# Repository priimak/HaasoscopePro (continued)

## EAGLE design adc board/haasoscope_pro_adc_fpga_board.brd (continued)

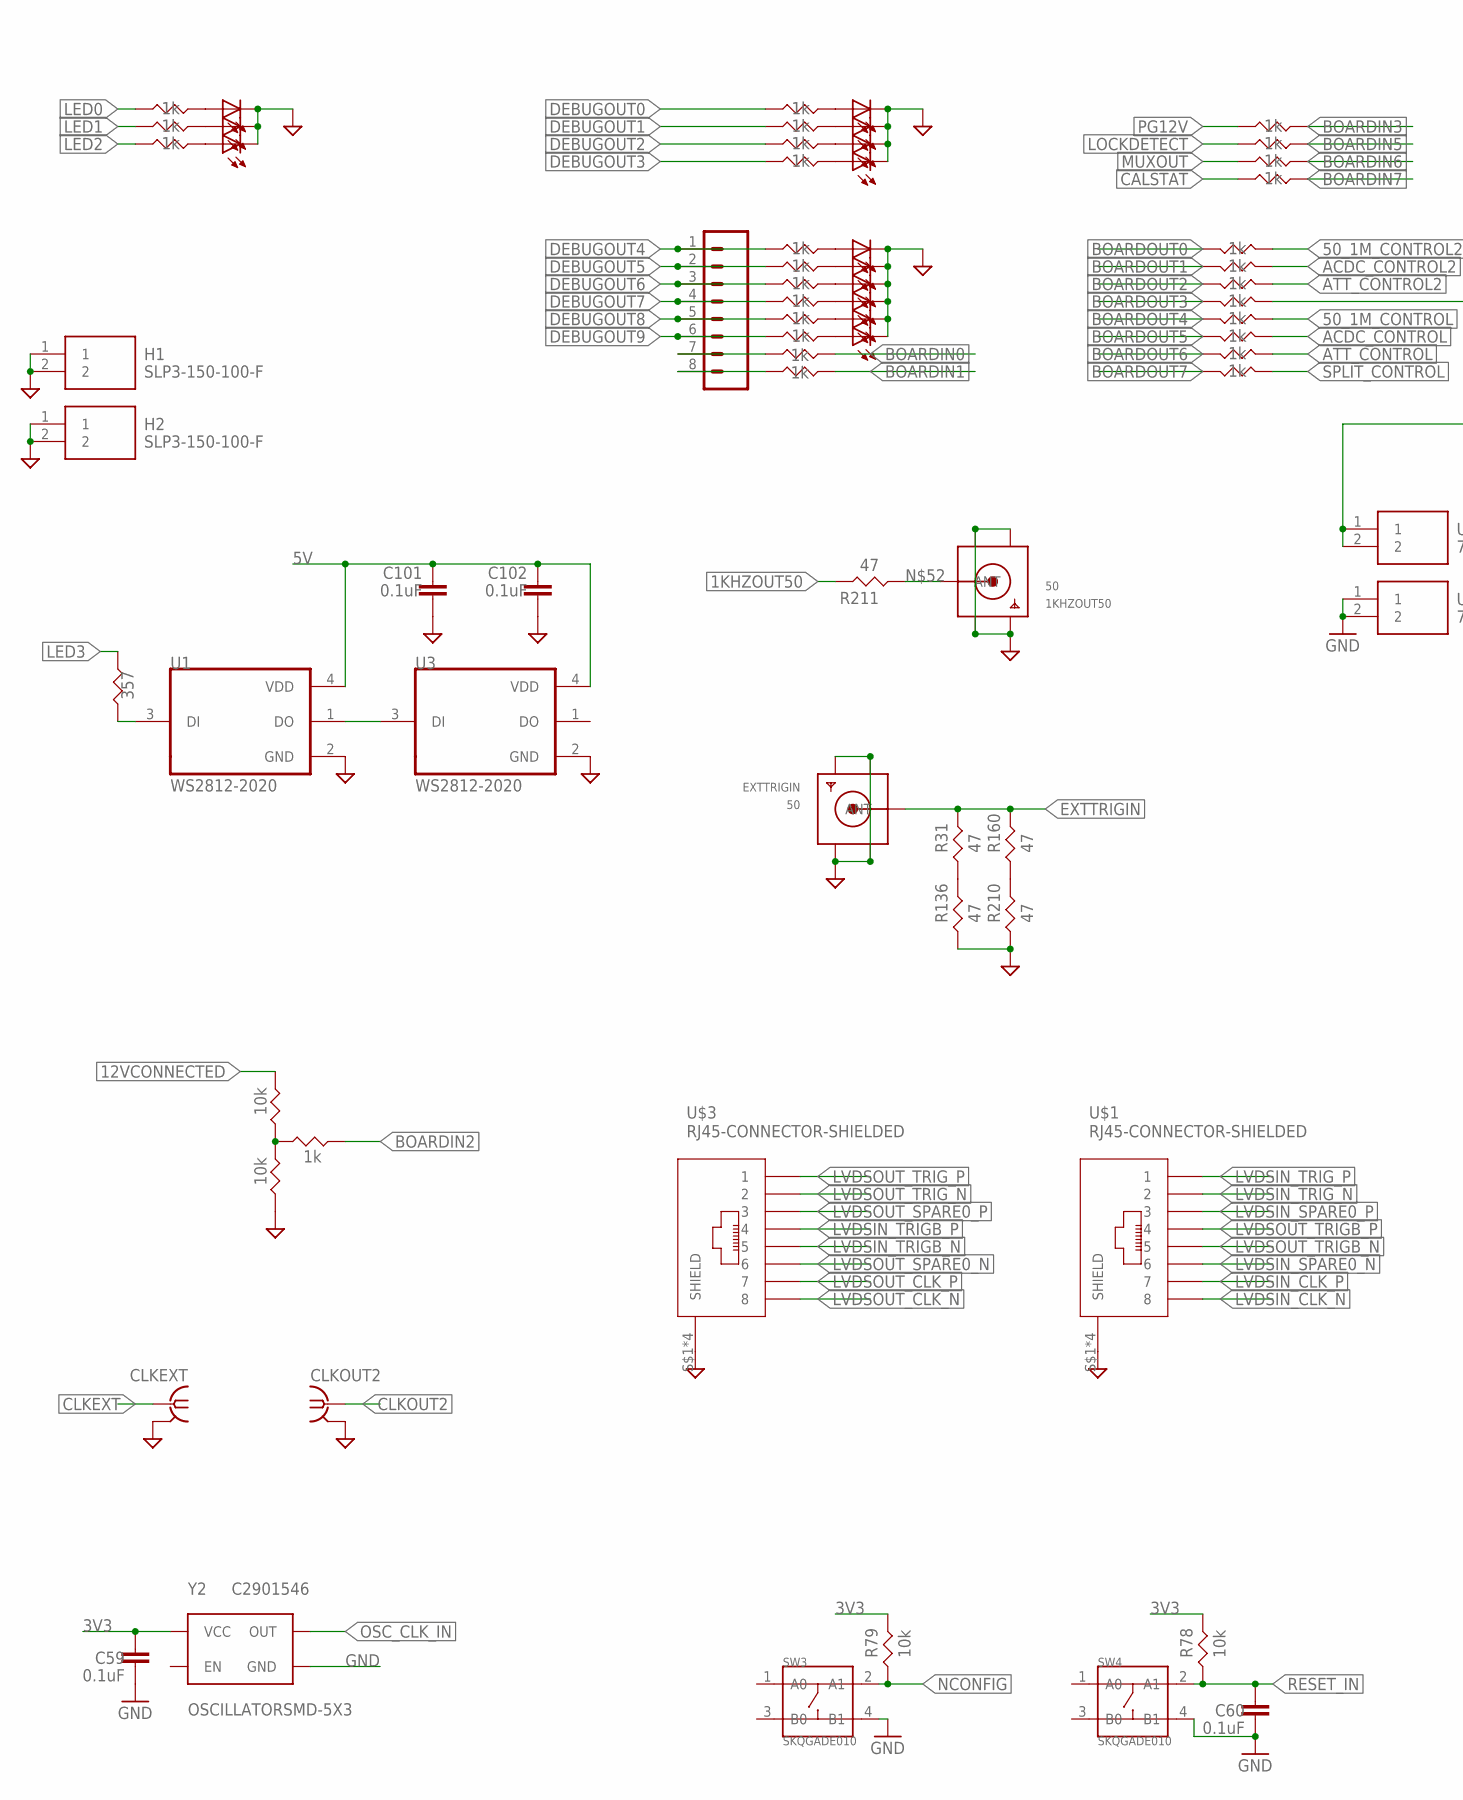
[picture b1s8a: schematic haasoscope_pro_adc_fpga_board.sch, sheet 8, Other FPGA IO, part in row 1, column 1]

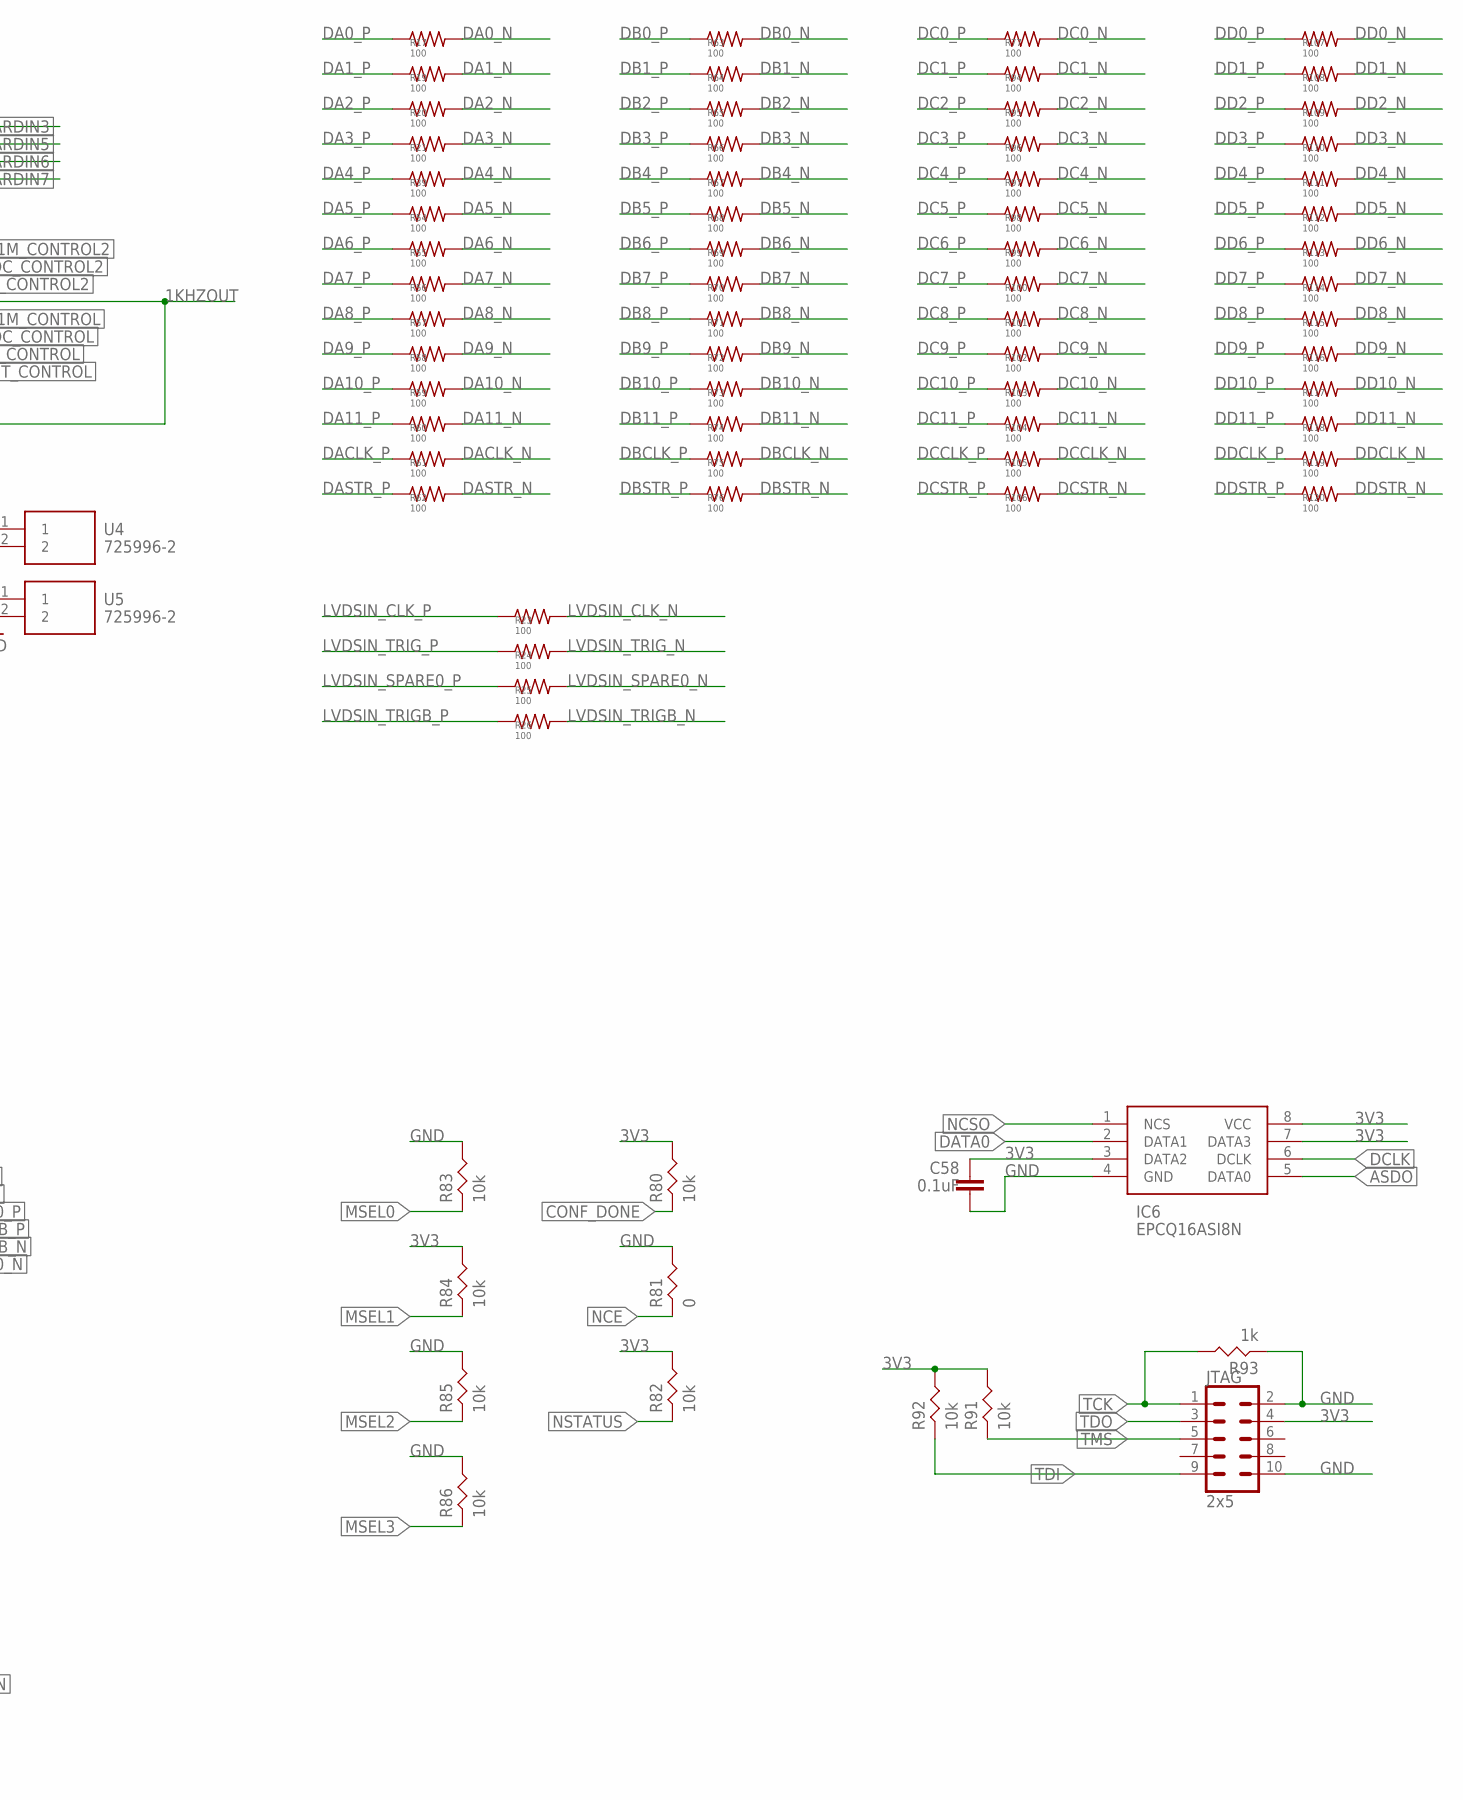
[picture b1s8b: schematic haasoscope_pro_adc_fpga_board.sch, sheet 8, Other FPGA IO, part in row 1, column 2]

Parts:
1KHZOUT50: 50; SMA_EDGELAUNCH
C58, C59, C60, C101, C102: 0.1uF; RESC0402_N
CLKEXT: BU-SMB-V
CLKOUT2: BU-SMB-V
EXTTRIGIN: 50; SMA_EDGELAUNCH
H1, H2: SLP3-150-100-F; SLP3150100F
IC6: EPCQ16ASI8N; SOIC127P600X175-8N
J11: 8pin; 1X08
JTAG: 2x5; 2X5-SHROUDED
LED25, LED26, LED27, LED28, LED29, LED30, LED41, LED42, LED43, LED45, LED46, LED47, LED48: red; CHIP-LED0603
R6, R7, R8, R9, R10, R11, R12, R13, R16, R22, R32, R33, R34, R35, R36, R37, R46, R47, R48, R49, R51, R52, R53, R93, R206, R236, R238, R243, R244: 1k; RES-0402
R17, R19, R20, R21, R23, R24, R25, R26, R39, R54, R55, R56, R57, R58, R59, R60, R61, R62, R63, R64, R65, R66, R67, R68, R69, R70, R71, R72, R73, R74, R75, R76, R77, R94, R95, R96, R97, R98, R99, R100, R101, R102, R103, R104, R105, R106, R107, R108, R109, R110, R111, R112, R113, R114, R115, R116, R117, R118, R119, R120: 100; R0201
R31, R136, R160, R210, R211: 47; RES-0402
R50: 357; RES-0402
R78, R79, R80, R82, R83, R84, R85, R86, R91, R92, R167, R246: 10k; RES-0402
R81: 0; RES-0402
SW3, SW4: SKQGADE010; SW4-SMD-5.2X5.2X1.5MM
U1, U3: WS2812-2020; LED_WS2812-2020
U4, U5: 725996-2; 7259962
U$1, U$3: RJ45-CONNECTOR-SHIELDED; RJ45_THT_RA_AMPH-FRJAE448
Y2: OSCILLATORSMD-5X3; OSCILLATOR-SMD-5X3.2; LCSC C2901546

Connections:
1KHZOUT: R206.P$1, U4.1, U4.2
1KHZOUT50: R211.P$2; also elsewhere on the board
3V3: C58.2, C59.2, IC6.3 (DATA2), IC6.7 (DATA3), IC6.8 (VCC), JTAG.4, R78.P$2, R79.P$2, R80.P$2, R82.P$2, R84.P$2, R91.P$2, R92.P$2, Y2.4 (VCC); also elsewhere on the board
5V: C101.2, C102.2, U1.4 (VDD), U3.4 (VDD); also elsewhere on the board
12VCONNECTED: R167.P$2; also elsewhere on the board
50_1M_CONTROL: R8.P$1; also elsewhere on the board
50_1M_CONTROL2: R12.P$1; also elsewhere on the board
ACDC_CONTROL: R9.P$1; also elsewhere on the board
ACDC_CONTROL2: R13.P$1; also elsewhere on the board
ASDO: IC6.5 (DATA0); also elsewhere on the board
ATT_CONTROL: R10.P$1; also elsewhere on the board
ATT_CONTROL2: R22.P$1; also elsewhere on the board
BOARDIN0: R243.P$1; also elsewhere on the board
BOARDIN1: R244.P$1; also elsewhere on the board
BOARDIN2: R238.P$2; also elsewhere on the board
BOARDIN3: R236.P$2; also elsewhere on the board
BOARDIN5: R7.P$2; also elsewhere on the board
BOARDIN6: R6.P$2; also elsewhere on the board
BOARDIN7: R16.P$2; also elsewhere on the board
BOARDOUT0: R12.P$2; also elsewhere on the board
BOARDOUT1: R13.P$2; also elsewhere on the board
BOARDOUT2: R22.P$2; also elsewhere on the board
BOARDOUT3: R206.P$2; also elsewhere on the board
BOARDOUT4: R8.P$2; also elsewhere on the board
BOARDOUT5: R9.P$2; also elsewhere on the board
BOARDOUT6: R10.P$2; also elsewhere on the board
BOARDOUT7: R11.P$2; also elsewhere on the board
CALSTAT: R16.P$1; also elsewhere on the board
CLKEXT: CLKEXT.1; also elsewhere on the board
CLKOUT2: CLKOUT2.1; also elsewhere on the board
CONF_DONE: R80.P$1; also elsewhere on the board
DA0_N: R17.2; also elsewhere on the board
DA0_P: R17.1; also elsewhere on the board
DA1_N: R19.2; also elsewhere on the board
DA1_P: R19.1; also elsewhere on the board
DA2_N: R20.2; also elsewhere on the board
DA2_P: R20.1; also elsewhere on the board
DA3_N: R21.2; also elsewhere on the board
DA3_P: R21.1; also elsewhere on the board
DA4_N: R39.2; also elsewhere on the board
DA4_P: R39.1; also elsewhere on the board
DA5_N: R54.2; also elsewhere on the board
DA5_P: R54.1; also elsewhere on the board
DA6_N: R55.2; also elsewhere on the board
DA6_P: R55.1; also elsewhere on the board
DA7_N: R56.2; also elsewhere on the board
DA7_P: R56.1; also elsewhere on the board
DA8_N: R57.2; also elsewhere on the board
DA8_P: R57.1; also elsewhere on the board
DA9_N: R58.2; also elsewhere on the board
DA9_P: R58.1; also elsewhere on the board
DA10_N: R59.2; also elsewhere on the board
DA10_P: R59.1; also elsewhere on the board
DA11_N: R60.2; also elsewhere on the board
DA11_P: R60.1; also elsewhere on the board
DACLK_N: R61.2; also elsewhere on the board
DACLK_P: R61.1; also elsewhere on the board
DASTR_N: R62.2; also elsewhere on the board
DASTR_P: R62.1; also elsewhere on the board
DATA0: IC6.2 (DATA1); also elsewhere on the board
DB0_N: R63.2; also elsewhere on the board
DB0_P: R63.1; also elsewhere on the board
DB1_N: R64.2; also elsewhere on the board
DB1_P: R64.1; also elsewhere on the board
DB2_N: R65.2; also elsewhere on the board
DB2_P: R65.1; also elsewhere on the board
DB3_N: R66.2; also elsewhere on the board
DB3_P: R66.1; also elsewhere on the board
DB4_N: R67.2; also elsewhere on the board
DB4_P: R67.1; also elsewhere on the board
DB5_N: R68.2; also elsewhere on the board
DB5_P: R68.1; also elsewhere on the board
DB6_N: R69.2; also elsewhere on the board
DB6_P: R69.1; also elsewhere on the board
DB7_N: R70.2; also elsewhere on the board
DB7_P: R70.1; also elsewhere on the board
DB8_N: R71.2; also elsewhere on the board
DB8_P: R71.1; also elsewhere on the board
DB9_N: R72.2; also elsewhere on the board
DB9_P: R72.1; also elsewhere on the board
DB10_N: R73.2; also elsewhere on the board
DB10_P: R73.1; also elsewhere on the board
DB11_N: R74.2; also elsewhere on the board
DB11_P: R74.1; also elsewhere on the board
DBCLK_N: R75.2; also elsewhere on the board
DBCLK_P: R75.1; also elsewhere on the board
DBSTR_N: R76.2; also elsewhere on the board
DBSTR_P: R76.1; also elsewhere on the board
DC0_N: R77.2; also elsewhere on the board
DC0_P: R77.1; also elsewhere on the board
DC1_N: R94.2; also elsewhere on the board
DC1_P: R94.1; also elsewhere on the board
DC2_N: R95.2; also elsewhere on the board
DC2_P: R95.1; also elsewhere on the board
DC3_N: R96.2; also elsewhere on the board
DC3_P: R96.1; also elsewhere on the board
DC4_N: R97.2; also elsewhere on the board
DC4_P: R97.1; also elsewhere on the board
DC5_N: R98.2; also elsewhere on the board
DC5_P: R98.1; also elsewhere on the board
DC6_N: R99.2; also elsewhere on the board
DC6_P: R99.1; also elsewhere on the board
DC7_N: R100.2; also elsewhere on the board
DC7_P: R100.1; also elsewhere on the board
DC8_N: R101.2; also elsewhere on the board
DC8_P: R101.1; also elsewhere on the board
DC9_N: R102.2; also elsewhere on the board
DC9_P: R102.1; also elsewhere on the board
DC10_N: R103.2; also elsewhere on the board
DC10_P: R103.1; also elsewhere on the board
DC11_N: R104.2; also elsewhere on the board
DC11_P: R104.1; also elsewhere on the board
DCCLK_N: R105.2; also elsewhere on the board
DCCLK_P: R105.1; also elsewhere on the board
DCLK: IC6.6 (DCLK); also elsewhere on the board
DCSTR_N: R106.2; also elsewhere on the board
DCSTR_P: R106.1; also elsewhere on the board
DD0_N: R107.2; also elsewhere on the board
DD0_P: R107.1; also elsewhere on the board
DD1_N: R108.2; also elsewhere on the board
DD1_P: R108.1; also elsewhere on the board
DD2_N: R109.2; also elsewhere on the board
DD2_P: R109.1; also elsewhere on the board
DD3_N: R110.2; also elsewhere on the board
DD3_P: R110.1; also elsewhere on the board
DD4_N: R111.2; also elsewhere on the board
DD4_P: R111.1; also elsewhere on the board
DD5_N: R112.2; also elsewhere on the board
DD5_P: R112.1; also elsewhere on the board
DD6_N: R113.2; also elsewhere on the board
DD6_P: R113.1; also elsewhere on the board
DD7_N: R114.2; also elsewhere on the board
DD7_P: R114.1; also elsewhere on the board
DD8_N: R115.2; also elsewhere on the board
DD8_P: R115.1; also elsewhere on the board
DD9_N: R116.2; also elsewhere on the board
DD9_P: R116.1; also elsewhere on the board
DD10_N: R117.2; also elsewhere on the board
DD10_P: R117.1; also elsewhere on the board
DD11_N: R118.2; also elsewhere on the board
DD11_P: R118.1; also elsewhere on the board
DDCLK_N: R119.2; also elsewhere on the board
DDCLK_P: R119.1; also elsewhere on the board
DDSTR_N: R120.2; also elsewhere on the board
DDSTR_P: R120.1; also elsewhere on the board
DEBUGOUT0: R49.P$1; also elsewhere on the board
DEBUGOUT1: R48.P$1; also elsewhere on the board
DEBUGOUT2: R47.P$1; also elsewhere on the board
DEBUGOUT3: R46.P$1; also elsewhere on the board
DEBUGOUT4: J11.1, R37.P$1; also elsewhere on the board
DEBUGOUT5: J11.2, R36.P$1; also elsewhere on the board
DEBUGOUT6: J11.3, R35.P$1; also elsewhere on the board
DEBUGOUT7: J11.4, R34.P$1; also elsewhere on the board
DEBUGOUT8: J11.5, R33.P$1; also elsewhere on the board
DEBUGOUT9: J11.6, R32.P$1; also elsewhere on the board
EXTTRIGIN: EXTTRIGIN.P (ANT), R31.P$2, R160.P$2; also elsewhere on the board
GND: 1KHZOUT50.GND@1 (GND4), 1KHZOUT50.GND@2 (GND3), 1KHZOUT50.GND@3 (GND2), 1KHZOUT50.GND@4 (GND1), C58.1, C59.1, C60.1, C101.1, C102.1, CLKEXT.2, CLKEXT.3 (2), CLKEXT.4 (2), CLKEXT.5 (2), CLKOUT2.2, CLKOUT2.3 (2), CLKOUT2.4 (2), CLKOUT2.5 (2), EXTTRIGIN.GND@1 (GND4), EXTTRIGIN.GND@2 (GND3), EXTTRIGIN.GND@3 (GND2), EXTTRIGIN.GND@4 (GND1), H1.1, H1.2, H2.1, H2.2, IC6.4 (GND), JTAG.2, JTAG.10, LED25.C, LED26.C, LED27.C, LED28.C, LED29.C, LED30.C, LED41.C, LED42.C, LED43.C, LED45.C, LED46.C, LED47.C, LED48.C, R81.P$2, R83.P$2, R85.P$2, R86.P$2, R93.P$1, R136.P$1, R210.P$1, R246.P$1, SW3.4 (B1), SW4.4 (B1), U1.2 (GND), U3.2 (GND), U5.1, U5.2, U$1.S$1 (SHIELD), U$1.S$2 (SHIELD), U$1.S$3 (SHIELD), U$1.S$4 (SHIELD), U$3.S$1 (SHIELD), U$3.S$2 (SHIELD), U$3.S$3 (SHIELD), U$3.S$4 (SHIELD), Y2.2 (GND); also elsewhere on the board
LED0: R53.P$1; also elsewhere on the board
LED1: R52.P$1; also elsewhere on the board
LED2: R51.P$1; also elsewhere on the board
LED3: R50.P$1; also elsewhere on the board
LOCKDETECT: R7.P$1; also elsewhere on the board
LVDSIN_CLK_N: R23.2, U$1.P$8 (8); also elsewhere on the board
LVDSIN_CLK_P: R23.1, U$1.P$7 (7); also elsewhere on the board
LVDSIN_SPARE0_N: R25.2, U$1.P$6 (6); also elsewhere on the board
LVDSIN_SPARE0_P: R25.1, U$1.P$3 (3); also elsewhere on the board
LVDSIN_TRIGB_N: R26.2, U$3.P$5 (5); also elsewhere on the board
LVDSIN_TRIGB_P: R26.1, U$3.P$4 (4); also elsewhere on the board
LVDSIN_TRIG_N: R24.2, U$1.P$2 (2); also elsewhere on the board
LVDSIN_TRIG_P: R24.1, U$1.P$1 (1); also elsewhere on the board
LVDSOUT_CLK_N: U$3.P$8 (8); also elsewhere on the board
LVDSOUT_CLK_P: U$3.P$7 (7); also elsewhere on the board
LVDSOUT_SPARE0_N: U$3.P$6 (6); also elsewhere on the board
LVDSOUT_SPARE0_P: U$3.P$3 (3); also elsewhere on the board
LVDSOUT_TRIGB_N: U$1.P$5 (5); also elsewhere on the board
LVDSOUT_TRIGB_P: U$1.P$4 (4); also elsewhere on the board
LVDSOUT_TRIG_N: U$3.P$2 (2); also elsewhere on the board
LVDSOUT_TRIG_P: U$3.P$1 (1); also elsewhere on the board
MSEL0: R83.P$1; also elsewhere on the board
MSEL1: R84.P$1; also elsewhere on the board
MSEL2: R85.P$1; also elsewhere on the board
MSEL3: R86.P$1; also elsewhere on the board
MUXOUT: R6.P$1; also elsewhere on the board
unnamed: R31.P$1, R136.P$2
unnamed: LED25.A, R37.P$2
unnamed: LED26.A, R36.P$2
unnamed: LED27.A, R35.P$2
unnamed: LED28.A, R34.P$2
unnamed: LED29.A, R33.P$2
unnamed: LED30.A, R32.P$2
unnamed: R160.P$1, R210.P$2
unnamed: LED41.A, R53.P$2
unnamed: LED42.A, R52.P$2
unnamed: LED43.A, R51.P$2
unnamed: R50.P$2, U1.3 (DI)
unnamed: LED45.A, R49.P$2
unnamed: LED46.A, R48.P$2
unnamed: LED47.A, R47.P$2
unnamed: LED48.A, R46.P$2
unnamed: 1KHZOUT50.P (ANT), R211.P$1
unnamed: J11.7, R243.P$2
unnamed: J11.8, R244.P$2
unnamed: R167.P$1, R238.P$1, R246.P$2
unnamed: U1.1 (DO), U3.3 (DI)
NCE: R81.P$1; also elsewhere on the board
NCONFIG: R79.P$1, SW3.2 (A1); also elsewhere on the board
NCSO: IC6.1 (NCS); also elsewhere on the board
NSTATUS: R82.P$1; also elsewhere on the board
OSC_CLK_IN: Y2.3 (OUT); also elsewhere on the board
PG12V: R236.P$1; also elsewhere on the board
RESET_IN: C60.2, R78.P$1, SW4.2 (A1); also elsewhere on the board
SPLIT_CONTROL: R11.P$1; also elsewhere on the board
TCK: JTAG.1, R93.P$2; also elsewhere on the board
TDI: JTAG.9, R92.P$1; also elsewhere on the board
TDO: JTAG.3; also elsewhere on the board
TMS: JTAG.5, R91.P$1; also elsewhere on the board

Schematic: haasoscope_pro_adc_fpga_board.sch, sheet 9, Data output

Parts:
C114, C115, C116, C117, C119, C121, C122, C123, C124, C125: 0.1uF; RESC0402_N
C118, C120, C126: 10uF; RESC0805_N
C127, C128: 16pF; RESC0402_N
FB2: 50mΩ 220Ω@100MHz 0603; 0603
IC8: FT232HQ; QFN48_8MM; JLC_ROTATION 270
IC9: 93LC56B; SOT23-6; LCSC C190271
R27, R38, R121, R123: 10k; RES-0402
R28, R29, R40, R41, R157, R179: 1k; RES-0402
R182, R183: 5.1k; RES-0402
R184: 39; RES-0402
X1: USBC; USB_C_CUSB31-CFM2AX-01-X
Y3: 12MHz; CRYSTAL-SMD-5X3; LCSC C2901628

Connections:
3V3: IC8.32 (ACBUS8), R121.P$2, R123.P$2; also elsewhere on the board
5V: C117.2, IC8.40 (VREGIN); also elsewhere on the board
CC1: R183.P$2, X1.A5 (CC1)
CC2: R182.P$2, X1.B5 (CC2)
FTDI_AC0_RXF: IC8.21 (ACBUS0/TXDEN); also elsewhere on the board
FTDI_AC1_TXE: IC8.25 (ACBUS1); also elsewhere on the board
FTDI_AC2_RD: IC8.26 (ACBUS2); also elsewhere on the board
FTDI_AC3_WR: IC8.27 (ACBUS3/RXLED#); also elsewhere on the board
FTDI_AC4_SIWU: IC8.28 (ACBUS4/TXLED#), R121.P$1
FTDI_AC5_CLK: R184.P$2; also elsewhere on the board
FTDI_AC6_OE: IC8.30 (ACBUS6); also elsewhere on the board
FTDI_AC7_PWRSAV: IC8.31 (ACBUS7), R123.P$1
FTDI_DATA0: IC8.13 (ADBUS0/TXD); also elsewhere on the board
FTDI_DATA1: IC8.14 (ADBUS1/RXD); also elsewhere on the board
FTDI_DATA2: IC8.15 (ADBUS2/RTS#); also elsewhere on the board
FTDI_DATA3: IC8.16 (ADBUS3/CTS#); also elsewhere on the board
FTDI_DATA4: IC8.17 (ADBUS4/DTR#); also elsewhere on the board
FTDI_DATA5: IC8.18 (ADBUS5/DSR#); also elsewhere on the board
FTDI_DATA6: IC8.19 (ADBUS6/DCD#); also elsewhere on the board
FTDI_DATA7: IC8.20 (ADBUS7/RI#); also elsewhere on the board
GND: C114.1, C115.1, C116.1, C117.1, C118.1, C119.1, C120.1, C121.1, C122.1, C123.1, C124.1, C125.1, C126.1, C127.2, C128.2, IC8.4 (AGND), IC8.9 (AGND), IC8.10 (GND), IC8.11 (GND), IC8.22 (GND), IC8.23 (GND), IC8.33 (ACBUS9), IC8.35 (GND), IC8.36 (GND), IC8.41 (AGND), IC8.42 (TEST), IC8.47 (GND), IC8.48 (GND), IC8.THERMAL (PAD), IC9.2 (GND), R41.P$1, R182.P$1, R183.P$1, X1.A1B12 (GND), X1.B1A12 (GND); also elsewhere on the board
unnamed: R27.P$1, R28.P$2
unnamed: R28.P$1, R29.P$2
unnamed: R38.P$1, R40.P$2
unnamed: R40.P$1, R41.P$2
unnamed: R157.P$1, R179.P$2
unnamed: C127.1, IC8.1 (OSCIN), Y3.3 (2)
unnamed: C128.1, IC8.2 (OSCOUT), Y3.1
unnamed: IC8.34 (!RESET), R27.P$2
unnamed: IC8.43 (EEDATA), IC9.3 (DI), R157.P$2
unnamed: IC8.45 (EECS), IC9.5 (CS)
unnamed: IC8.44 (EECLK), IC9.4 (CLK)
unnamed: IC9.1 (DO), R179.P$1
unnamed: IC8.29 (ACBUS5), R184.P$1
REF: IC8.5 (REF), R38.P$2
USB_D_N: IC8.7 (USBD+), X1.A6 (D+), X1.B6 (D+)
USB_D_P: IC8.6 (USBD-), X1.A7 (D-), X1.B7 (D-)
VBUS: C118.2, FB2.1, X1.A4B9 (VBUS), X1.B4A9 (VBUS)
VBUSOUT: C126.2, FB2.2; also elsewhere on the board
VCC1V8: C114.2, IC8.38 (VCCCORE)
VCC3V3: C116.2, C119.2, C120.2, C121.2, C122.2, C123.2, C124.2, C125.2, IC8.3 (VPHY), IC8.8 (VPLL), IC8.12 (VCCIO), IC8.24 (VCCIO), IC8.39 (VCCD), IC8.46 (VCCIO), IC9.6 (VCC), R29.P$1
VCCA_FTDI: C115.2, IC8.37 (VCCA)

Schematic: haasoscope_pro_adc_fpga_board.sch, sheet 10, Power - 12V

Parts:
C81, C166, C290, C291, C292, C293: 22uF; RESC0805_N
C171, C172: 1000uF; EEE0JA152UAP; LCSC C401766
C242, C243, C287, C289, C319, C320, C321, C322: 10uF; RESC0805_N
C283, C318: 0.1uF; RESC0402_N; LCSC C307331
C284, C286: 0.1uF; RESC0402_N
C285: 1uF; RESC0402_N
CN2: 12Vin; DCJACK_2MM_PTH
J30, J45, J46: 2p-2.54; H2-2.54
L2, L14: 10uH; CDRH125; LCSC C339970
LED2, LED3, LED4: red; CHIP-LED0603
PS14: LMR33630ADDA; SOIC127P600X170-9N; LCSC C841384
Q2: FDN340P; SOT-23; MPN P-MOS AO3401A
R148, R151, R212, R234, R239: 10k; RES-0402
R152, R165, R217, R235: 5.1k; RES-0402
R233: 100k; RES-0402
R237: 1k; RES-0402

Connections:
5V: C166.1, C172.1 (+), J45.1, L2.2, R148.P$2; also elsewhere on the board
5VDIRTY: C81.1, C171.1 (+), C286.1, C287.1, C289.1, C290.1, C291.1, C292.1, C293.1, J46.2, L2.1, L14.2, LED3.A, Q2.2 (S), R233.P$2, R237.P$2
12V: C242.1, C283.1, C319.1, C320.1, CN2.PWR, J30.2, LED2.A, PS14.2 (VIN), PS14.3 (EN)
12VCONNECTED: CN2.GNDBREAK, R237.P$1, R239.P$1; also elsewhere on the board
GND: C81.2, C166.2, C171.2 (-), C172.2 (-), C243.2, C285.2, C286.2, C287.2, C289.2, C290.2, C291.2, C292.2, C293.2, C318.2, C321.2, C322.2, CN2.GND, J30.1, J45.2, J46.1, PS14.1 (PGND), PS14.9 (EP), R148.P$1, R152.P$1, R165.P$1, R217.P$1, R235.P$1; also elsewhere on the board
unnamed: R151.P$2, R234.P$1
unnamed: R151.P$1, R152.P$2
unnamed: LED2.C, R217.P$2
unnamed: LED3.C, R235.P$2
unnamed: Q2.1 (G), R239.P$2
unnamed: LED4.C, R165.P$2
unnamed: C242.2, C243.1
unnamed: C284.1, L14.1, PS14.8 (SW)
unnamed: C284.2, PS14.7 (BOOT)
unnamed: PS14.5 (FB), R233.P$1, R234.P$2
unnamed: C285.1, PS14.6 (VCC)
unnamed: C283.2, C318.1
unnamed: C319.2, C321.1
unnamed: C320.2, C322.1
PG12V: PS14.4 (PG), R212.P$2; also elsewhere on the board
VBUSOUT: LED4.A, Q2.3 (D); also elsewhere on the board
VCCIO2V5: R212.P$1; also elsewhere on the board

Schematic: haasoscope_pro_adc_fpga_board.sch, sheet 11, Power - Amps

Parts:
C73, C74, C77, C250, C252, C254, C279, C280, C282: 0.1uF; RESC0402_N
C76, C251, C253, C288: 10uF; RESC0805_N
C83: 1000uF; EEE0JA152UAP; LCSC C401766
C281: 1uF; RESC0402_N
C294, C295, C296, C297: 22uF; RESC0805_N
D10: B340A; SMA-DIODE; LCSC C64982
IC10, IC25: TPS72325DBVR; SOT95P280X145-5N
IC26: TPS7A7200RGTR; QFN50P300X300X100-17N
J4, J34, J35, J44: 2p-2.54; H2-2.54
L13: 10uH; CDRH125; LCSC C339970
PS13: LMR33630ADDA; SOIC127P600X170-9N; LCSC C841384
R209, R231, R232: 100k; RES-0402
R216: 10k; RES-0402

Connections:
2V5+: C253.1, C254.1, IC26.1 (SNS), IC26.15 (OUT_1), IC26.16 (OUT_2), J35.2, R216.P$1; also elsewhere on the board
2V5-1: C251.1, IC25.5 (OUT), J34.1; also elsewhere on the board
2V5-2: C76.1, IC10.5 (OUT), J4.1; also elsewhere on the board
3V0-: C77.1, C83.2 (-), C252.1, C279.2, C281.2, C282.2, C288.2, C294.2, C295.2, C296.2, C297.2, D10.A, IC10.2 (IN), IC25.2 (IN), J44.2, PS13.1 (PGND), PS13.9 (EP), R209.P$1, R232.P$1
3V3: C73.1, IC26.12 (EN), IC26.13 (IN_1), IC26.14 (IN_2); also elsewhere on the board
5V: C279.1, C288.1, PS13.2 (VIN), PS13.3 (EN); also elsewhere on the board
GND: C73.2, C74.2, C76.2, C77.2, C83.1 (+), C250.2, C251.2, C252.2, C253.2, C254.2, C282.1, C294.1, C295.1, C296.1, C297.1, D10.C, IC10.1 (GND), IC25.1 (GND), IC26.7 (GND), IC26.8 (400MV), IC26.10 (1.6V), IC26.17 (EP), J4.2, J34.2, J35.1, J44.1, L13.2, R231.P$2; also elsewhere on the board
unnamed: C74.1, IC10.4 (NR/FB)
unnamed: C250.1, IC25.4 (NR/FB)
unnamed: C280.1, L13.1, PS13.8 (SW)
unnamed: C280.2, PS13.7 (BOOT)
unnamed: PS13.5 (FB), R209.P$2, R231.P$1, R232.P$2
unnamed: C281.1, PS13.6 (VCC)
PG25: IC26.3 (PG), R216.P$2

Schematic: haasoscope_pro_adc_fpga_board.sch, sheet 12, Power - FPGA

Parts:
C52, C170, C173, C257: 10uF; RESC0805_N
C53, C54, C258, C271, C272, C274, C275, C276, C278: 0.1uF; RESC0402_N
C99, C168: 1000uF; EEE0JA152UAP; LCSC C401766
C273, C277: 1uF; RESC0402_N
C298, C299, C300, C301, C302, C303, C304, C305: 22uF; RESC0805_N
IC7, IC28: TPS7A7200RGTR; QFN50P300X300X100-17N
J3, J37, J42, J43: 2p-2.54; H2-2.54
L11, L12: 10uH; CDRH125; LCSC C339970
PS11, PS12: LMR33630ADDA; SOIC127P600X170-9N; LCSC C841384
R137, R227, R229, R230: 100k; RES-0402
R161, R220: 10k; RES-0402
R228: 56k; RES-0402

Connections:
1V2: C52.1, C53.1, IC7.1 (SNS), IC7.15 (OUT_1), IC7.16 (OUT_2), J3.2, R161.P$1; also elsewhere on the board
1V5D: C54.1, C99.1 (+), C278.1, C298.1, C299.1, C300.1, C301.1, IC7.12 (EN), IC7.13 (IN_1), IC7.14 (IN_2), J43.1, L12.2, R229.P$2
2V5D: C257.1, C258.1, IC28.1 (SNS), IC28.15 (OUT_1), IC28.16 (OUT_2), J37.2, R220.P$1; also elsewhere on the board
2V8D: C168.1 (+), C274.1, C302.1, C303.1, C304.1, C305.1, IC28.12 (EN), IC28.13 (IN_1), IC28.14 (IN_2), J42.1, L11.2, R227.P$2
5V: C170.1, C173.1, C271.1, C275.1, PS11.2 (VIN), PS11.3 (EN), PS12.2 (VIN), PS12.3 (EN); also elsewhere on the board
GND: C52.2, C53.2, C54.2, C99.2 (-), C168.2 (-), C170.2, C173.2, C257.2, C258.2, C271.2, C273.2, C274.2, C275.2, C277.2, C278.2, C298.2, C299.2, C300.2, C301.2, C302.2, C303.2, C304.2, C305.2, IC7.5 (100MV), IC7.6 (200MV), IC7.7 (GND), IC7.8 (400MV), IC7.17 (EP), IC28.7 (GND), IC28.8 (400MV), IC28.10 (1.6V), IC28.17 (EP), J3.1, J37.1, J42.2, J43.2, PS11.1 (PGND), PS11.9 (EP), PS12.1 (PGND), PS12.9 (EP), R137.P$1, R228.P$1; also elsewhere on the board
unnamed: R137.P$2, R230.P$1
unnamed: C272.1, L11.1, PS11.8 (SW)
unnamed: C272.2, PS11.7 (BOOT)
unnamed: PS11.5 (FB), R227.P$1, R228.P$2
unnamed: C273.1, PS11.6 (VCC)
unnamed: C276.1, L12.1, PS12.8 (SW)
unnamed: C276.2, PS12.7 (BOOT)
unnamed: PS12.5 (FB), R229.P$1, R230.P$2
unnamed: C277.1, PS12.6 (VCC)
PG1V2: IC7.3 (PG), R161.P$2
PG2V5D: IC28.3 (PG), R220.P$2

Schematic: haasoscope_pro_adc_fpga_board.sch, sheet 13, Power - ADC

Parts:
C100, C165, C167: 1000uF; EEE0JA152UAP; LCSC C401766
C174, C175, C176, C244, C246, C248, C255: 10uF; RESC0805_N
C245, C247, C249, C256, C259, C260, C262, C263, C264, C266, C267, C268, C270: 0.1uF; RESC0402_N
C261, C265, C269: 1uF; RESC0402_N
C306, C307, C308, C309, C310, C311, C312, C313, C314, C315, C316, C317: 22uF; RESC0805_N
IC22, IC23, IC24, IC27: TPS7A7200RGTR; QFN50P300X300X100-17N
J31, J32, J33, J36, J39, J40, J41: 2p-2.54; H2-2.54
L1, L9, L10: 10uH; CDRH125; LCSC C339970
LED1: red; CHIP-LED0603
PS2, PS9, PS10: LMR33630ADDA; SOIC127P600X170-9N; LCSC C841384
R163, R221, R223, R224, R225, R226: 100k; RES-0402
R204, R205: 1M; RES-0402
R213, R214, R215, R219: 10k; RES-0402
R218: 5.1k; RES-0402
R222: 39k; RES-0402

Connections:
1V5: C165.1 (+), C266.1, C310.1, C311.1, C312.1, C313.1, IC24.13 (IN_1), IC24.14 (IN_2), J40.1, L9.2, R223.P$2
2V2: C167.1 (+), C270.1, C306.1, C307.1, C308.1, C309.1, IC23.12 (EN), IC23.13 (IN_1), IC23.14 (IN_2), IC27.12 (EN), IC27.13 (IN_1), IC27.14 (IN_2), J41.1, L10.2, R225.P$2
3V3: C244.1, C245.1, IC22.1 (SNS), IC22.15 (OUT_1), IC22.16 (OUT_2), J31.2, LED1.A, R213.P$1; also elsewhere on the board
3V7: C100.1 (+), C262.1, C314.1, C315.1, C316.1, C317.1, IC22.12 (EN), IC22.13 (IN_1), IC22.14 (IN_2), J39.1, L1.2, R221.P$2
5V: C174.1, C175.1, C176.1, C259.1, C263.1, C267.1, PS2.2 (VIN), PS2.3 (EN), PS9.2 (VIN), PS9.3 (EN), PS10.2 (VIN), PS10.3 (EN); also elsewhere on the board
GND: C100.2 (-), C165.2 (-), C167.2 (-), C174.2, C175.2, C176.2, C244.2, C245.2, C246.2, C247.2, C248.2, C249.2, C255.2, C256.2, C259.2, C261.2, C262.2, C263.2, C265.2, C266.2, C267.2, C269.2, C270.2, C306.2, C307.2, C308.2, C309.2, C310.2, C311.2, C312.2, C313.2, C314.2, C315.2, C316.2, C317.2, IC22.7 (GND), IC22.8 (400MV), IC22.9 (800MV), IC22.10 (1.6V), IC22.17 (EP), IC23.6 (200MV), IC23.7 (GND), IC23.8 (400MV), IC23.9 (800MV), IC23.17 (EP), IC24.6 (200MV), IC24.7 (GND), IC24.8 (400MV), IC24.17 (EP), IC27.6 (200MV), IC27.7 (GND), IC27.8 (400MV), IC27.9 (800MV), IC27.17 (EP), J31.1, J32.1, J33.1, J36.1, J39.2, J40.2, J41.2, PS2.1 (PGND), PS2.9 (EP), PS9.1 (PGND), PS9.9 (EP), PS10.1 (PGND), PS10.9 (EP), R163.P$1, R204.P$1, R205.P$1, R218.P$1, R222.P$1, R226.P$1; also elsewhere on the board
unnamed: R163.P$2, R224.P$1
unnamed: C260.1, L1.1, PS2.8 (SW)
unnamed: C260.2, PS2.7 (BOOT)
unnamed: PS2.5 (FB), R221.P$1, R222.P$2
unnamed: C261.1, PS2.6 (VCC)
unnamed: C264.1, L9.1, PS9.8 (SW)
unnamed: C264.2, PS9.7 (BOOT)
unnamed: PS9.5 (FB), R223.P$1, R224.P$2
unnamed: C265.1, PS9.6 (VCC)
unnamed: C268.1, L10.1, PS10.8 (SW)
unnamed: C268.2, PS10.7 (BOOT)
unnamed: PS10.5 (FB), R204.P$2, R205.P$2, R225.P$1, R226.P$2
unnamed: C269.1, PS10.6 (VCC)
unnamed: LED1.C, R218.P$2
PG1V1: IC24.3 (PG), R215.P$2
PG1V9: IC23.3 (PG), IC24.12 (EN), R214.P$2
PG1V9D: IC27.3 (PG), R219.P$2
PG3V3: IC22.3 (PG), R213.P$2
V11_IN: C248.1, C249.1, IC24.1 (SNS), IC24.15 (OUT_1), IC24.16 (OUT_2), J33.2, R215.P$1; also elsewhere on the board
V19_IN: C246.1, C247.1, IC23.1 (SNS), IC23.15 (OUT_1), IC23.16 (OUT_2), J32.2, R214.P$1; also elsewhere on the board
VLVDS_IN: C255.1, C256.1, IC27.1 (SNS), IC27.15 (OUT_1), IC27.16 (OUT_2), J36.2, R219.P$1; also elsewhere on the board

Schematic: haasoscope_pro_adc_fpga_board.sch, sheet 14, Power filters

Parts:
C5, C15, C25, C35, C45: NFM31PC276B0J3L; NFM31HK103R1H3L
C6, C8, C10, C13, C16, C18, C21, C24, C26, C28, C34, C36, C38, C40, C41, C42, C43, C46, C48: 10uF; RESC0805_N
C7, C9, C12, C17, C19, C20, C23, C27, C29, C31, C33, C37, C39, C47, C49, C61, C62, C63, C64, C65, C66, C67, C68, C69, C70, C71: 0.1uF; RESC0402_N
C11, C14, C22, C30, C32: 1uF; RESC0402_N
R15, R18, R87, R88, R89, R90: 0; RES-0402

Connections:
1V2: R88.P$1, R89.P$1; also elsewhere on the board
2V5D: R87.P$1, R90.P$1; also elsewhere on the board
3V3: R15.P$1, R18.P$1; also elsewhere on the board
GND: C5.2 (GND_1), C5.4 (GND_2), C6.1, C7.1, C8.1, C9.1, C10.1, C11.1, C12.1, C13.1, C14.1, C15.2 (GND_1), C15.4 (GND_2), C16.1, C17.1, C18.1, C19.1, C20.1, C21.1, C22.1, C23.1, C24.1, C25.2 (GND_1), C25.4 (GND_2), C26.1, C27.1, C28.1, C29.1, C30.1, C31.1, C32.1, C33.1, C34.1, C35.2 (GND_1), C35.4 (GND_2), C36.1, C37.1, C38.1, C39.1, C40.1, C41.1, C42.1, C43.1, C45.2 (GND_1), C45.4 (GND_2), C46.1, C47.1, C48.1, C49.1, C61.1, C62.1, C63.1, C64.1, C65.1, C66.1, C67.1, C68.1, C69.1, C70.1, C71.1; also elsewhere on the board
V11_IN: C35.1 (IN), C36.2, C37.2, C45.1 (IN), C46.2, C47.2; also elsewhere on the board
V19_IN: C15.1 (IN), C16.2, C17.2, C25.1 (IN), C26.2, C27.2; also elsewhere on the board
VA11: C21.2, C22.2, C23.2, C32.2, C33.2, C35.3 (OUT), C38.2, C39.2; also elsewhere on the board
VA19: C13.2, C14.2, C20.2, C25.3 (OUT), C28.2, C29.2; also elsewhere on the board
VCCA: C41.2, C71.2, R90.P$2; also elsewhere on the board
VCCINT: C43.2, C69.2, R88.P$2; also elsewhere on the board
VCCIO2V5: C40.2, C61.2, C62.2, C65.2, C66.2, C67.2, C68.2, R87.P$2; also elsewhere on the board
VCCIO3V3: C34.2, C63.2, C64.2, R18.P$2; also elsewhere on the board
VCCPLL: C42.2, C70.2, R89.P$2; also elsewhere on the board
VD11: C24.2, C30.2, C31.2, C45.3 (OUT), C48.2, C49.2; also elsewhere on the board
VDDD33: R15.P$2; also elsewhere on the board
VDDL19: C15.3 (OUT), C18.2, C19.2; also elsewhere on the board
VLVDS: C5.3 (OUT), C8.2, C9.2, C10.2, C11.2, C12.2; also elsewhere on the board
VLVDS_IN: C5.1 (IN), C6.2, C7.2; also elsewhere on the board

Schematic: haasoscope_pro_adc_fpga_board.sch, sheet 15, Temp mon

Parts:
C44, C50: 0.1uF; 0402_CAP
IC3: ADC122S021CIMM_NOPB; SOP65P490X110-8N
IC4: TLV9102IPWR; SOP65P640X120-8N
JST_FAN: Fan; 1X02
LED32: red; CHIP-LED0603
Q1: S8050; SOT-23; LCSC C7420370
R30: 1k; RES-0402
R122, R124, R126, R202, R203: 1k; 0402_RES
R125, R127, R130, R186, R198: 10k; 0402_RES
R128, R129: 0; 0402_RES
R207: NCP18WF104F03RC; R0603; MPN NCP18XH103F03RB; LCSC C13564
R208: 1k; R0402

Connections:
3V3: C44.1, C50.1, IC3.2 (VA), IC4.8 (V+), R127.1, R130.1; also elsewhere on the board
5V: JST_FAN.1; also elsewhere on the board
FAN-: JST_FAN.2, Q1.3 (C)
FAN_CONTROL: R30.P$1, R208.P$2; also elsewhere on the board
GND: C44.2, C50.2, IC3.3 (GND), IC4.4 (V-), LED32.C, Q1.2 (E), R124.1, R125.1, R128.2, R207.1; also elsewhere on the board
unnamed: Q1.1 (B), R208.P$1
unnamed: LED32.A, R30.P$2
unnamed: R127.2, R186.1
unnamed: R186.2, R198.1
unnamed: R122.2, R202.1
unnamed: R202.2, R203.1
SCLK3: IC3.8 (SCLK); also elsewhere on the board
SCS3_SLOWADC: IC3.1 (!CS); also elsewhere on the board
SDI3: IC3.6 (DIN); also elsewhere on the board
SDO3_SLOWADC: IC3.7 (DOUT); also elsewhere on the board
SLOWADCIN1: IC4.3 (IN1+), R129.2
SLOWADCIN1-: IC4.2 (IN1-), R124.2, R203.2
SLOWADCIN2: IC4.5 (IN2+), R130.2, R207.2
SLOWADCIN2-: IC4.6 (IN2-), R125.2, R126.1
SLOWADCOUT1: IC3.5 (IN1), IC4.1 (OUT1), R122.1
SLOWADCOUT2: IC3.4 (IN2), IC4.7 (OUT2), R126.2
TDIODE1: R129.1, R198.2; also elsewhere on the board
TDIODE2: R128.1; also elsewhere on the board
